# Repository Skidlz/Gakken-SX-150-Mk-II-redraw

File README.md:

# Gakken-SX-150-Mk-II-redraw
A recreation of the Gakken SX-150 Mk II in Eagle CAD format

## Schematic

## PCB

## Original

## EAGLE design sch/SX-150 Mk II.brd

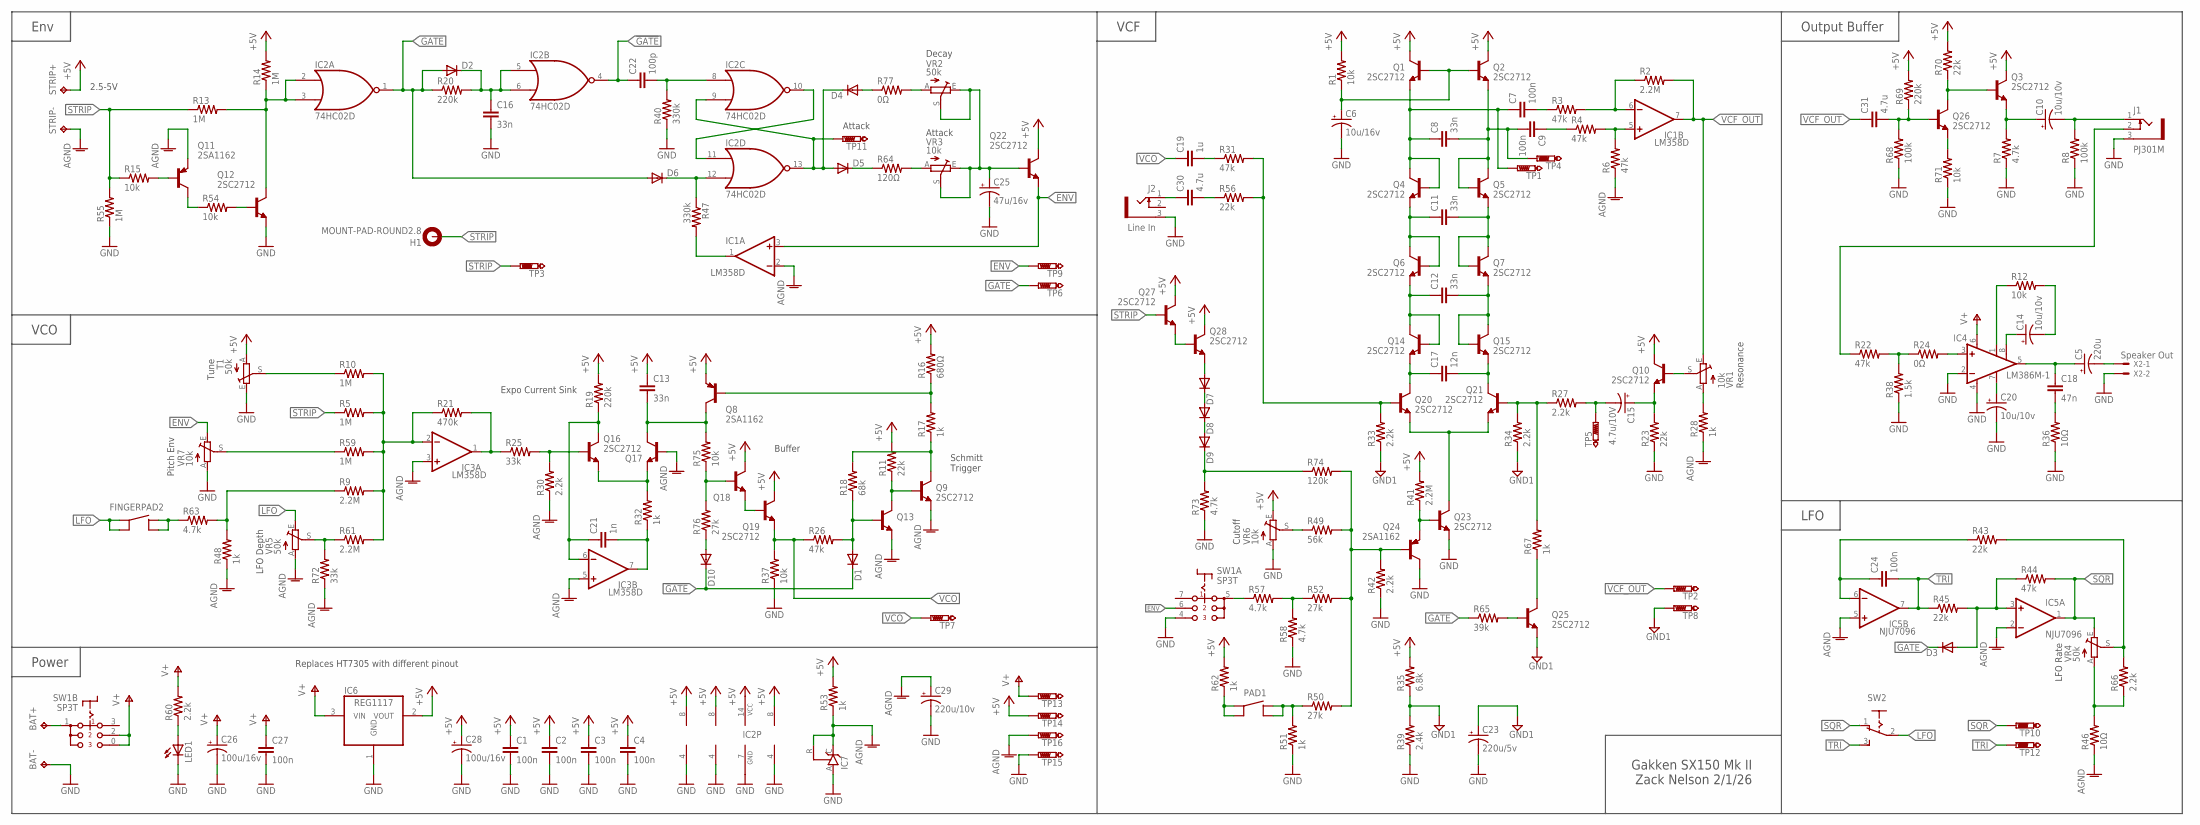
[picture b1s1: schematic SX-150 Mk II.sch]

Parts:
BAT+: TPPAD1-13; P1-13
BAT-: TPPAD1-13; P1-13
C1, C2, C3, C4, C7, C9, C24, C27: 100n; C0603
C5: 220u; E2,5-6
C6: 10u/16v; E2,5-6
C8, C11, C12, C13, C16: 33n; C0603
C10, C14, C20: 10u/10v; E2,5-6
C15: 4.7u/10V; E2,5-6
C17: 12n; C0603
C18: 47n; C0603
C19: 1u; C0603
C21: 1n; C0603
C22: 100p; C0603
C23: 220u/5v; E2,5-6
C25: 47u/16v; E2,5-6
C26, C28: 100u/16v; E2,5-6
C29: 220u/10v; E2,5-6
C30, C31: 4.7u; C0603
D1, D10: DIODE-DO41-7.6; DO41-7.6
D2, D3, D4, D5, D6, D7, D8, D9: DIODE-MINIMELF; MINIMELF
FINGERPAD2: GAKKEN-PAD
H1: MOUNT-PAD-ROUND2.8; 2,8-PAD
IC1, IC3: LM358D; SO08
IC2: 74HC02D; SO14
IC4: LM386M-1; SO08
IC5: NJU7096; SO08
IC6: REG1117; SOT223
IC7: TL431CLP; TO92-CLP
J1: PJ301M; JACK-3.5-NOHOLE
J2: Line In; JACK-3.5-NOHOLE
LED1: LED3MM
PAD1: GAKKEN-PAD
Q1, Q2, Q3, Q4, Q5, Q6, Q7, Q9, Q10, Q12, Q13, Q14, Q15, Q16, Q17, Q18, Q19, Q20, Q21, Q22, Q23, Q25, Q26, Q27, Q28: 2SC2712; SOT23-BEC
Q8, Q11, Q24: 2SA1162; SOT23-BEC
R1, R12, R15, R37, R54, R71, R75: 10k; R0603
R2, R9, R41, R61: 2.2M; R0603
R3, R4, R6, R22, R26, R31, R44: 47k; R0603
R5, R10, R13, R14, R55, R59: 1M; R0603
R7, R57, R58, R63, R73: 4.7k; R0603
R8, R68: 100k; R0603
R11, R23, R43, R45, R56, R70: 22k; R0603
R16: 680Ω; R0603
R17, R28, R32, R48, R51, R53, R62, R67: 1k; R0603
R18: 68k; R0603
R19, R20, R69: 220k; R0603
R21: 470k; R0603
R24, R77: 0Ω; R0603
R25, R72: 33k; R0603
R27, R30, R33, R34, R42, R60, R66: 2.2k; R0603
R35: 6.8k; R0603
R36, R46: 10Ω; R0603
R38: 1.5k; R0603
R39: 2.4k; R0603
R40, R47: 330k; R0603
R49: 56k; R0603
R50, R52, R76: 27k; R0603
R64: 120Ω; R0603
R65: 39k; R0603
R74: 120k; R0603
STRIP+: TPB1,27; B1,27
STRIP-: TPB1,27; B1,27
SW1: SP3T
SW2: M251
T1: 50k; CA9V
TP1, TP2, TP3, TP4, TP5, TP6, TP7, TP8, TP9, TP10, TP11, TP12, TP13, TP14, TP15, TP16: PTR1B1,27; B1,27
VR1, VR3, VR6, VR7: 10k; CA9V
VR2, VR4, VR5: 50k; CA9V
X2: Speaker Out; 22-23-2021

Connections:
!GATE: C22.1, D1.C, D3.C, D10.C, IC2.4 (O)
+5V: C1.1, C2.1, C3.1, C4.1, C13.1, C28.+, IC1.8 (V+), IC2.14 (VCC), IC3.8 (V+), IC5.8 (V+), IC6.2 (VOUT), Q1.C, Q2.C, Q3.C, Q8.E, Q10.C, Q18.C, Q19.C, Q22.C, Q27.C, Q28.C, R1.2, R11.2, R14.2, R16.2, R19.2, R35.2, R41.2, R53.2, R62.2, R69.2, R70.2, STRIP+.TP, T1.A, TP14.TP, VR6.E
AGND: C29.+, IC1.2 (-IN), IC3.3 (+IN), IC3.5 (+IN), IC5.2 (-IN), IC5.5 (+IN), IC7.C, IC7.R, Q9.E, Q11.E, Q13.E, Q17.B, R6.1, R28.1, R30.1, R46.1, R48.1, R53.1, R72.1, STRIP-.TP, TP16.TP, VR5.A
ENV: IC1.3 (+IN), Q22.E, SW1.6 (T2), TP9.TP, VR7.E
GATE: D2.A, D6.A, IC2.1 (O), R20.1, R65.1, TP6.TP
GND: BAT-.TP, C1.2, C2.2, C3.2, C4.2, C6.-, C16.2, C20.-, C23.-, C25.-, C26.-, C27.2, C28.-, C29.-, IC1.4 (V-), IC2.7 (GND), IC3.4 (V-), IC4.2 (-IN), IC4.4 (GND), IC5.4 (V-), IC6.1 (GND), IC7.A, J1.3 (1), J2.3 (1), LED1.K (C), Q12.E, Q23.E, Q24.C, R7.1, R8.1, R23.1, R36.1, R37.1, R38.1, R39.1, R40.1, R42.1, R51.1, R55.1, R58.1, R68.1, R71.1, R73.1, SW1.4 (T3), T1.E, TP15.TP, VR6.A, VR7.A, X2.2
GND1: C23.+, Q25.E, R33.1, R34.1, R35.1, R39.2, TP8.TP
LFO: FINGERPAD2.A0, FINGERPAD2.A1, SW2.2, VR5.E
unnamed: IC1.1 (OUT), R47.2
unnamed: D5.C, R64.1
unnamed: IC2.2 (I0), IC2.3 (I1), Q12.C, R13.2, R14.1
unnamed: IC2.10 (O), IC2.11 (I0)
unnamed: D4.C, D5.A, IC2.9 (I1), IC2.13 (O), TP11.TP
unnamed: C22.2, IC2.8 (I0), R40.2
unnamed: Q12.B, R54.2
unnamed: C16.1, D2.C, IC2.5 (I0), IC2.6 (I1), R20.2
unnamed: D6.C, IC2.12 (I1), R47.1
unnamed: D4.A, R77.1
unnamed: R77.2, VR2.A
unnamed: R64.2, VR3.A
unnamed: C25.+, Q22.B, VR2.E, VR2.S, VR3.E, VR3.S
unnamed: Q11.C, R54.1
unnamed: Q11.B, R15.2
unnamed: R61.1, R72.2, VR5.S
unnamed: C24.1, IC5.6 (-IN), R43.1
unnamed: IC3.2 (-IN), R5.2, R9.2, R10.2, R21.1, R59.2, R61.2
unnamed: D3.A, IC5.3 (+IN), R44.1, R45.2
unnamed: R46.2, R66.1, VR4.A
unnamed: R43.2, R66.2, VR4.S
unnamed: IC3.1 (OUT), R21.2, R25.1
unnamed: Q16.B, R25.2, R30.2
unnamed: R59.1, VR7.S
unnamed: R9.1, R48.2, R63.2
unnamed: R10.1, T1.S
unnamed: C13.2, Q8.C, Q17.C, R75.2
unnamed: Q8.B, R16.1, R17.2
unnamed: C21.2, IC3.7 (OUT), R32.1
unnamed: Q16.E, Q17.E, R32.2
unnamed: C21.1, IC3.6 (-IN), Q16.C, R19.1
unnamed: Q9.C, R17.1, R18.2
unnamed: Q18.B, R75.1, R76.2
unnamed: Q18.E, Q19.B
unnamed: BAT+.TP, SW1.1
unnamed: Q9.B, Q13.C, R11.1
unnamed: D1.A, Q13.B, R18.1, R26.2
unnamed: D10.A, R76.1
unnamed: C7.1, C8.1, Q1.E, Q4.B, Q4.C, TP1.TP
unnamed: C8.2, C9.2, Q2.E, Q5.B, Q5.C, TP4.TP
unnamed: C6.+, Q1.B, Q2.B, R1.1
unnamed: Q20.E, Q21.E, Q23.C
unnamed: C11.1, Q4.E, Q6.B, Q6.C
unnamed: C11.2, Q5.E, Q7.B, Q7.C
unnamed: Q20.B, R31.2, R33.2, R56.2
unnamed: C12.1, Q6.E, Q14.B, Q14.C
unnamed: C12.2, Q7.E, Q15.B, Q15.C
unnamed: C17.1, Q14.E, Q20.C
unnamed: C17.2, Q15.E, Q21.C
unnamed: Q21.B, R27.1, R34.2, R67.2
unnamed: C7.2, R3.1
unnamed: C9.1, R4.1
unnamed: IC1.6 (-IN), R2.1, R3.2
unnamed: IC1.5 (+IN), R4.2, R6.2
unnamed: Q23.B, Q24.E, R41.1
unnamed: Q25.C, R67.1
unnamed: Q25.B, R65.2
unnamed: C15.-, R27.2, TP5.TP
unnamed: C15.+, Q10.E, R23.2
unnamed: Q10.B, VR1.S
unnamed: R28.2, VR1.A
unnamed: Q24.B, R42.2, R49.2, R50.2, R52.2, R74.2
unnamed: R57.1, SW1.5 (P1)
unnamed: R49.1, VR6.S
unnamed: R52.1, R57.2, R58.2
unnamed: PAD1.B0, PAD1.B1, R50.1, R51.2
unnamed: C19.2, R31.1
unnamed: C30.2, R56.1
unnamed: C30.1, J2.1 (2)
unnamed: C31.2, Q26.B, R68.2, R69.1
unnamed: Q3.B, Q26.C, R70.1
unnamed: Q26.E, R71.2
unnamed: C10.+, Q3.E, R7.2
unnamed: C10.-, J1.1 (2), R8.2
unnamed: Q27.E, Q28.B
unnamed: PAD1.A0, PAD1.A1, R62.1
unnamed: D7.A, Q28.E
unnamed: D7.C, D8.A
unnamed: D8.C, D9.A
unnamed: D9.C, R73.2, R74.1
unnamed: FINGERPAD2.B0, FINGERPAD2.B1, R63.1
unnamed: C20.+, IC4.7 (BYPASS)
unnamed: C14.+, IC4.8 (GAIN)
unnamed: IC4.1 (GAIN), R12.1
unnamed: C14.-, R12.2
unnamed: C5.+, C18.1, IC4.5 (OUT)
unnamed: IC4.3 (+IN), R24.2
unnamed: C5.-, X2.1
unnamed: J1.2 (3), R22.1
unnamed: C18.2, R36.2
unnamed: R22.2, R24.1, R38.2
unnamed: LED1.A, R60.1
SQR: IC5.1 (OUT), R44.2, SW2.1 (O), TP10.TP, VR4.E
STRIP: H1.B2,8, Q27.B, R5.1, R13.1, R15.1, R55.2, TP3.TP
TRI: C24.2, IC5.7 (OUT), R45.1, SW2.3 (S), TP12.TP
V+: C26.+, C27.1, IC4.6 (VS), IC6.3 (VIN), R60.2, SW1.0 (T3), SW1.2 (T2), TP13.TP
VCF_OUT: C31.1, IC1.7 (OUT), R2.2, TP2.TP, VR1.E
VCO: C19.1, Q19.E, R26.1, R37.2, TP7.TP

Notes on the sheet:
Decay
Attack
2.5-5V
LFO Rate
Expo Current Sink
Buffer
Schmitt Trigger
VCO
LFO Depth
Cutoff
Replaces HT7305 with different pinout
Env
VCF
LFO
Output Buffer
Power
Gakken SX150 Mk II Zack Nelson 2/1/26
Resonance
Pitch Env
Tune

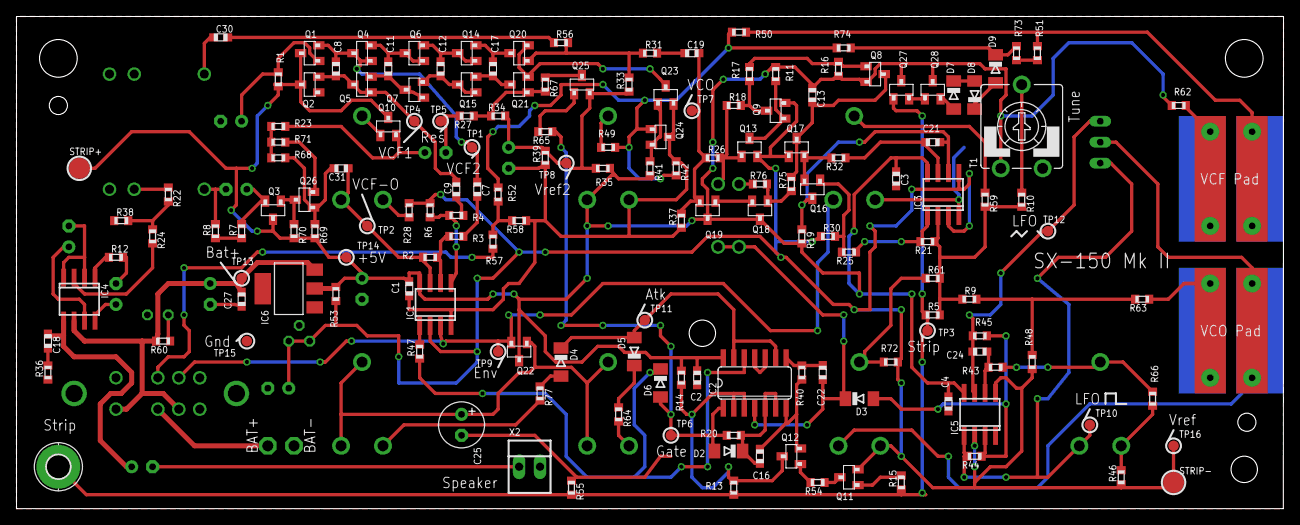
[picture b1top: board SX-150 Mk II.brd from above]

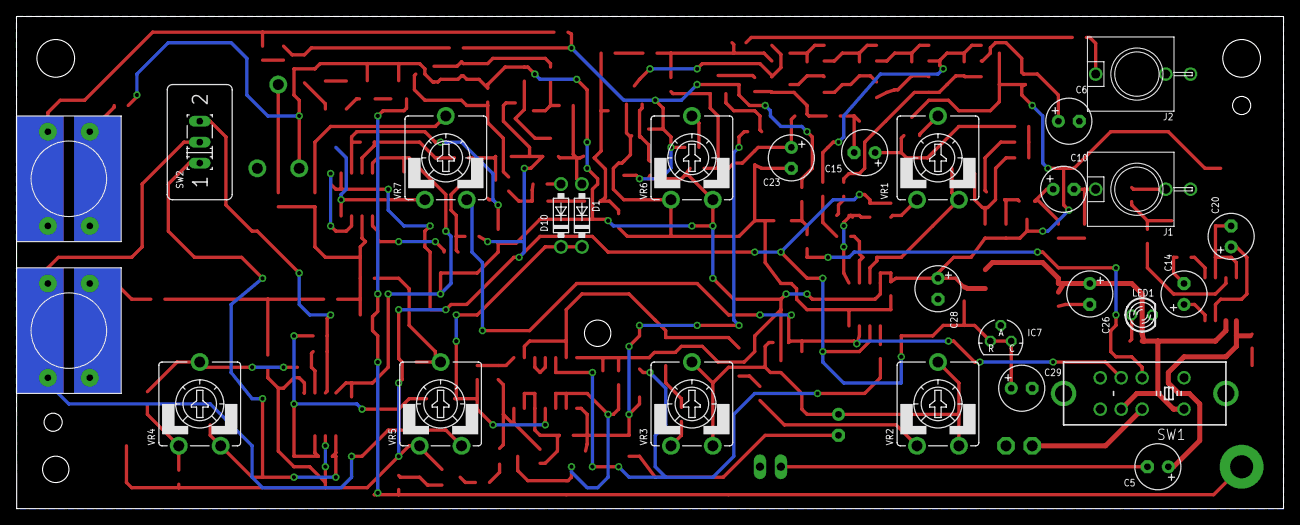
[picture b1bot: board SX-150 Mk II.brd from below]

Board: 2 copper layers, 153.7 x 59.7 mm, 189 parts (27 on the bottom side), 106 nets.

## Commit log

2026-02-01 Init files
2026-02-02 Updating board layout and adding gerbers
2026-02-02 Tweaking silkscreen
